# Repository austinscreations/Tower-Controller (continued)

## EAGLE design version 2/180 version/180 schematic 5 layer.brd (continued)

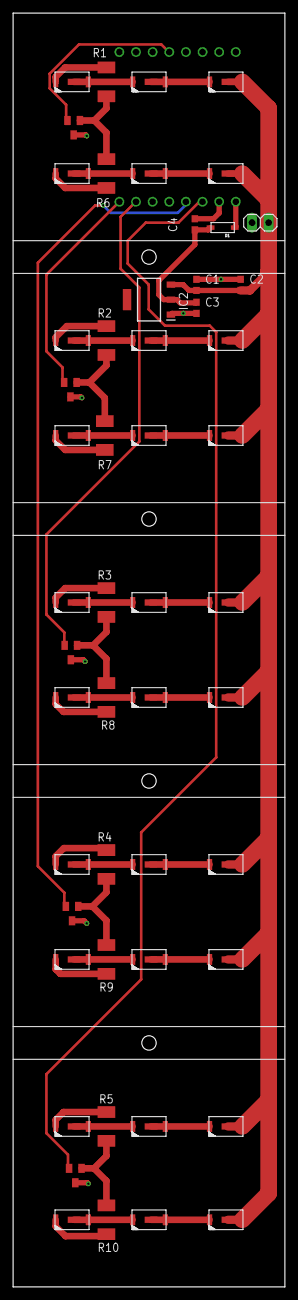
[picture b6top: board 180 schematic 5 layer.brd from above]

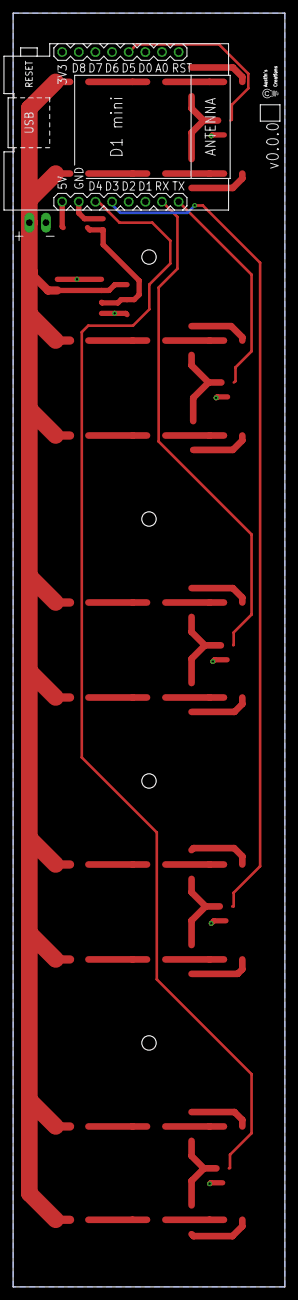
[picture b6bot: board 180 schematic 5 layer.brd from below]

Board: 2 copper layers, 41.5 x 194.5 mm, 54 parts (2 on the bottom side), 44 nets.

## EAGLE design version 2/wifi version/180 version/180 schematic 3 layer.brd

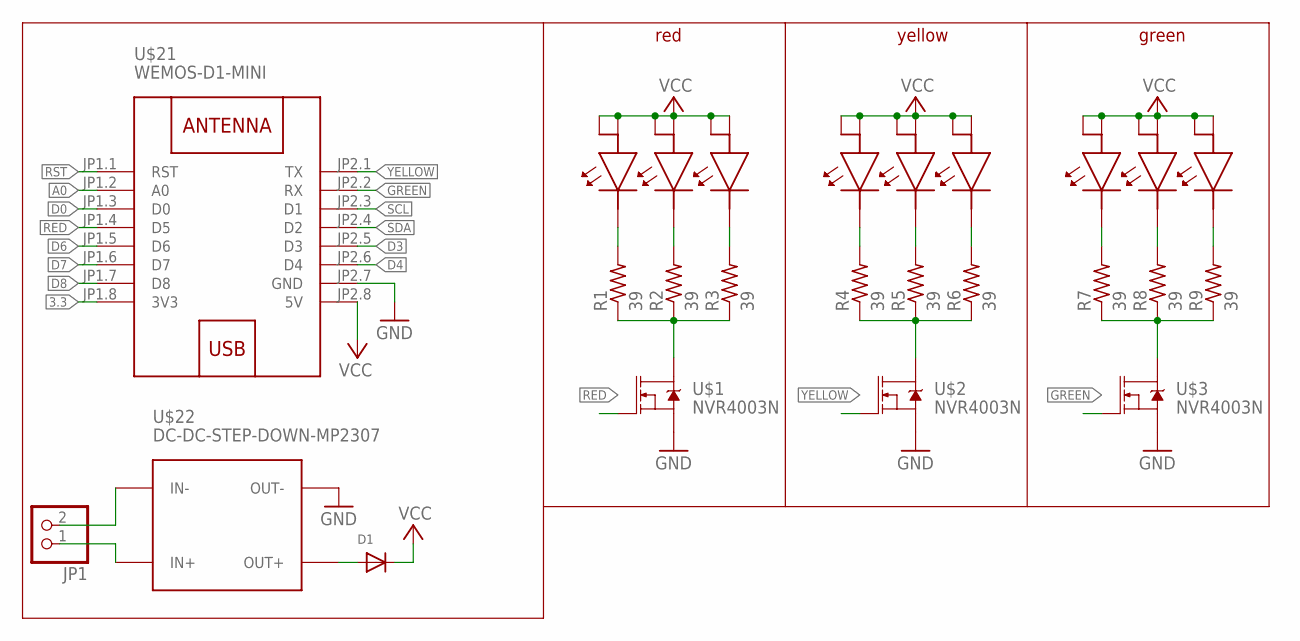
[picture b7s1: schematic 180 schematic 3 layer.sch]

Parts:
D1: DIODESOD-123; SOD-123
JP1: PINHD-1X2; 1X02
R1, R2, R3, R4, R5, R6, R7, R8, R9: 39; R1206W
U$1, U$2, U$3: NVR4003N; SOT23
U$6, U$7, U$8, U$9, U$10, U$11, U$12, U$13, U$14: 5730LED
U$21: WEMOS-D1-MINI
U$22: DC-DC-STEP-DOWN-MP2307

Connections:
3.3: U$21.JP1.8 (3V3)
A0: U$21.JP1.2 (A0)
D0: U$21.JP1.3 (D0)
D3: U$21.JP2.5 (D3)
D4: U$21.JP2.6 (D4)
D6: U$21.JP1.5 (D6)
D7: U$21.JP1.6 (D7)
D8: U$21.JP1.7 (D8)
GND: U$1.3 (S), U$2.3 (S), U$3.3 (S), U$21.JP2.7 (GND), U$22.OUT-
GREEN: U$3.2 (G), U$21.JP2.2 (RX)
unnamed: D1.A, U$22.OUT+
unnamed: JP1.2, U$22.IN-
unnamed: JP1.1, U$22.IN+
unnamed: R1.2, U$6.P$2
unnamed: R2.2, U$7.P$2
unnamed: R3.2, U$8.P$2
unnamed: R4.2, U$9.P$2
unnamed: R5.2, U$10.P$2
unnamed: R6.2, U$11.P$2
unnamed: R7.2, U$12.P$2
unnamed: R8.2, U$13.P$2
unnamed: R9.2, U$14.P$2
unnamed: R1.1, R2.1, R3.1, U$1.1 (D)
unnamed: R4.1, R5.1, R6.1, U$2.1 (D)
unnamed: R7.1, R8.1, R9.1, U$3.1 (D)
RED: U$1.2 (G), U$21.JP1.4 (D5)
RST: U$21.JP1.1 (RST)
SCL: U$21.JP2.3 (D1)
SDA: U$21.JP2.4 (D2)
VCC: D1.C, U$6.P$1, U$6.P$3, U$7.P$1, U$7.P$3, U$8.P$1, U$8.P$3, U$9.P$1, U$9.P$3, U$10.P$1, U$10.P$3, U$11.P$1, U$11.P$3, U$12.P$1, U$12.P$3, U$13.P$1, U$13.P$3, U$14.P$1, U$14.P$3, U$21.JP2.8 (5V)
YELLOW: U$2.2 (G), U$21.JP2.1 (TX)

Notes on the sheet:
red
yellow
green

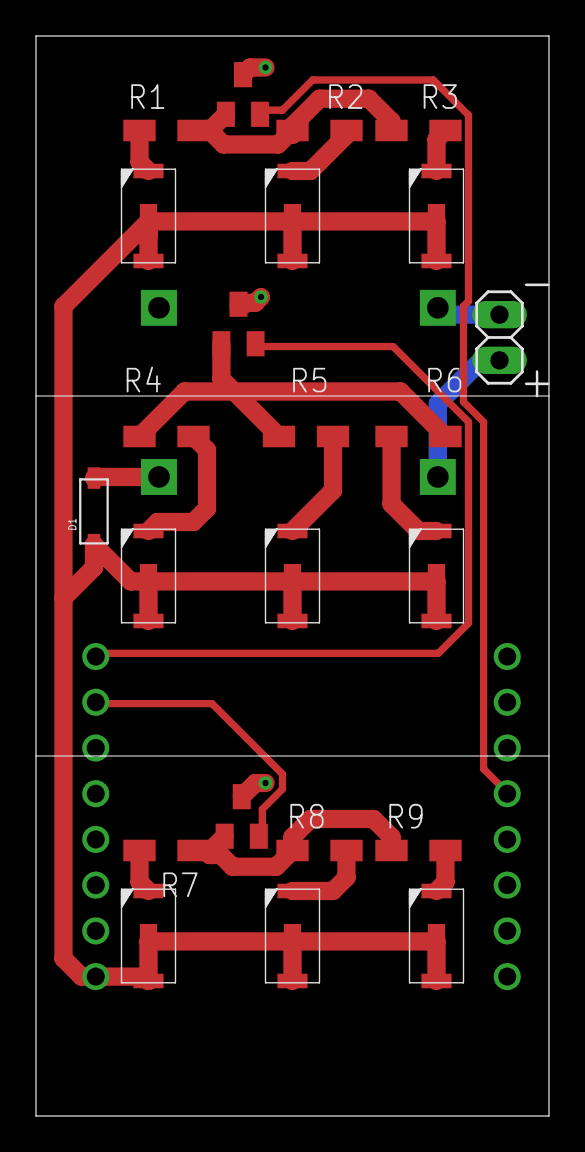
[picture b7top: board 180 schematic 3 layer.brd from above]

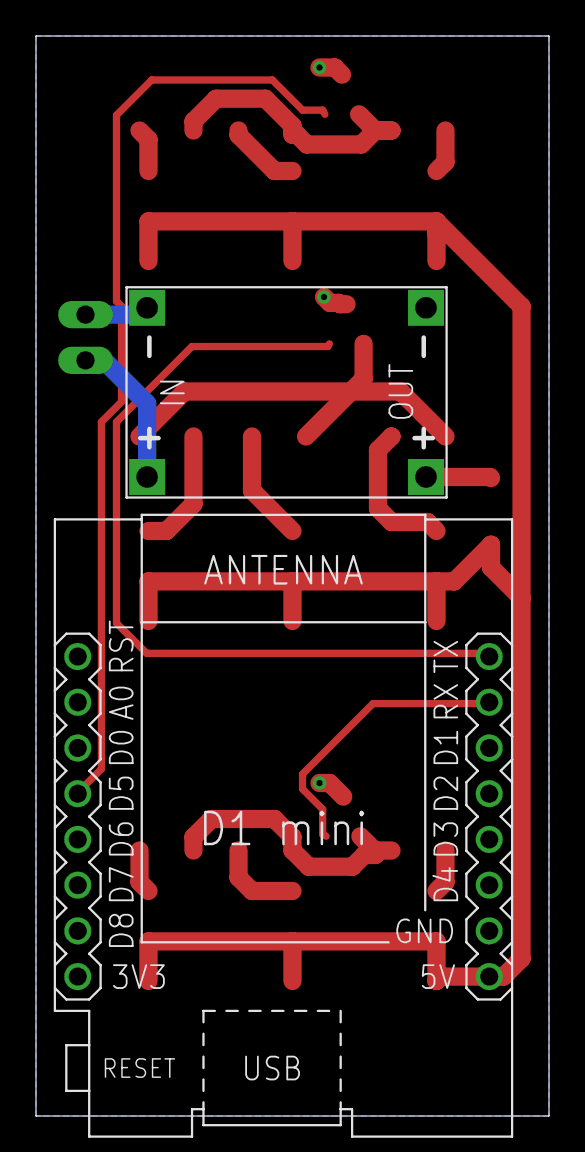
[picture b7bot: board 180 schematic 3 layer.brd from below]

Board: 2 copper layers, 28.5 x 60.0 mm, 25 parts (2 on the bottom side), 20 nets.

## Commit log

2022-01-15 remove repeated chunk of code
2022-01-26 new oxrs code + readme
2022-01-26 spelling
2022-02-02 new version to match changes to OXRS_SENSORS library
2022-02-05 bh1750 library changed
2022-02-05 fitment clearance around ethernet jack
2022-02-06 updating height to better fit sensors
2022-02-09 wrong values for OLED control fixed
2022-05-04 code is obsolete
2022-05-04 updating spelling and new code link
2022-12-27 add latest version
